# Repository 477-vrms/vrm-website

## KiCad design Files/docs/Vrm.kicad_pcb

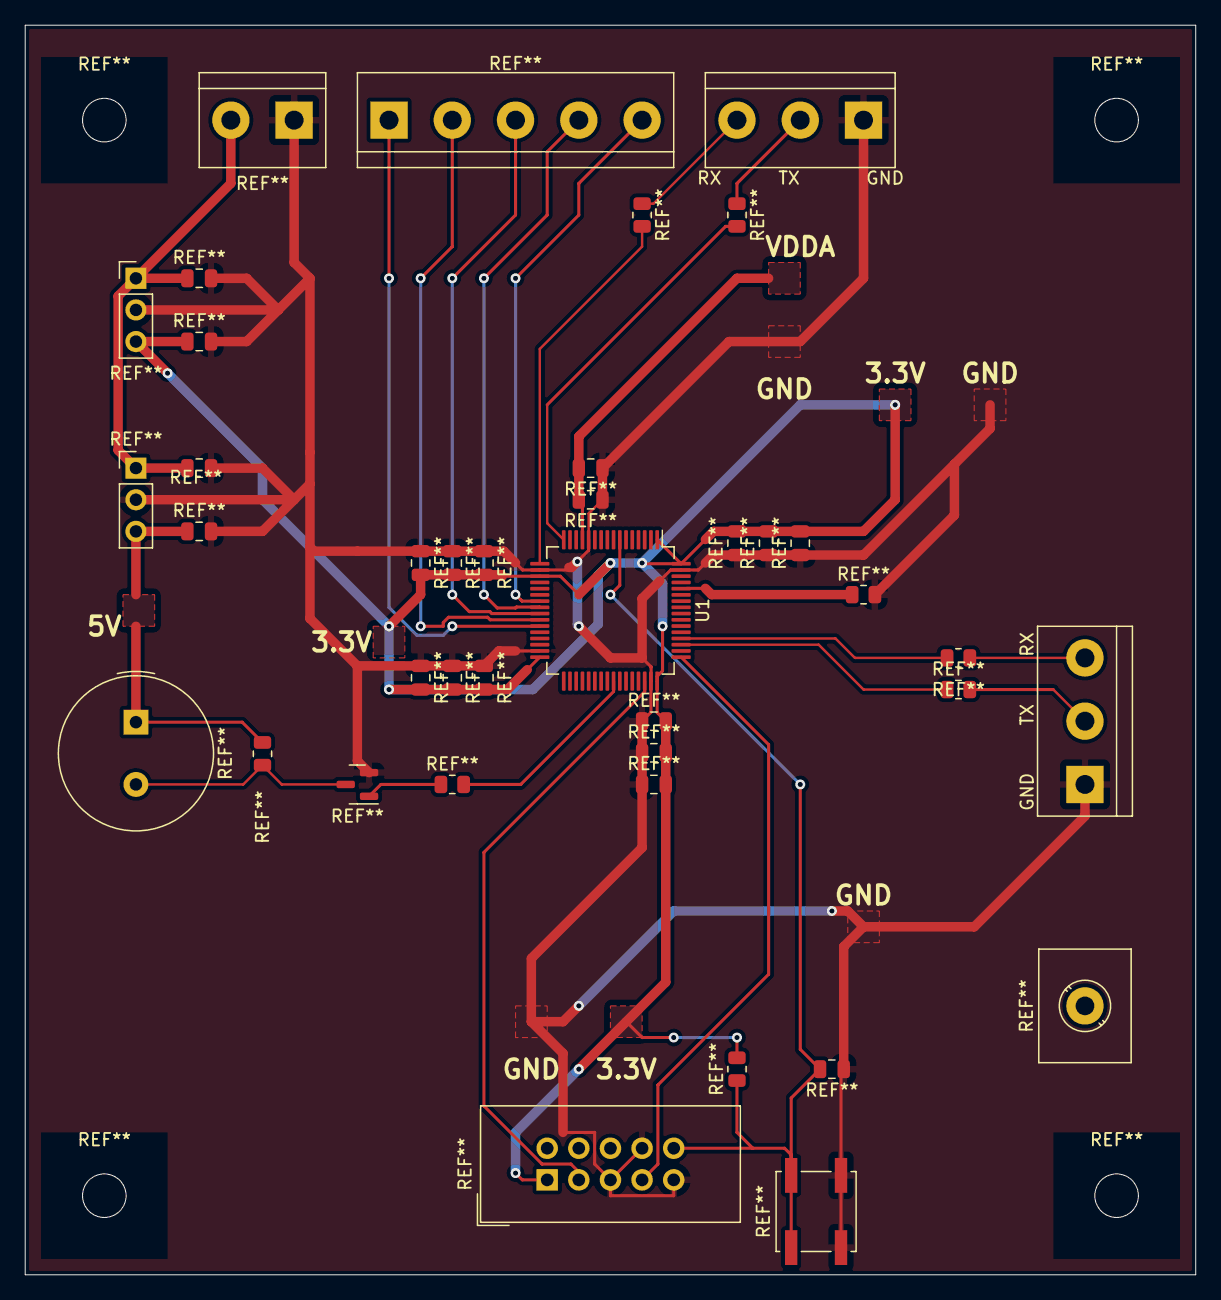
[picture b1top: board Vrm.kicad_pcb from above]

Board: 2 copper layers, 94.0 x 100.3 mm, 3 parts (0 on the bottom side), 2 nets.

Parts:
   RX      TX       GND: PI UART; TerminalBlock_bornier-3_P5.08mm
GND     TX     RX: Servo UART; TerminalBlock_bornier-3_P5.08mm
U1: STM32F091RCTx; LQFP-64_10x10mm_P0.5mm

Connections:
GND: RX TX GND.1, GND TX RX.1, U1.12 (VSSA), U1.18 (VSS), U1.31 (VSS), U1.47 (VSS), U1.63 (VSS)
VDD: U1.1 (VBAT), U1.19 (VDD), U1.32 (VDD), U1.48 (VDDIO2), U1.64 (VDD)

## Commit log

2022-01-19 Updated source link
2022-01-19 added github actions and edited the nav bar
2022-01-19 added github actions and edited the nav bar (#1)
2022-01-20 Added Changes for Matthew Wen
2022-01-20 Added Changes for Matthew Wen (#2)
2022-01-20 with document
2022-01-20 protyping potentially new website
2022-01-20 Brian profile
    member 2
2022-01-20 Update navbar.html
    oop
2022-01-21 Finished Writing Report
2022-01-21 Matt Wen Finished Writing Report (#3)
2022-01-21 Added James Information
2022-01-21 progress report
2022-01-21 prog report
2022-01-21 James' Week 2 Progress Report Created
2022-01-21 added documents
2022-01-26 Updated Content * Added PSSE onto website * Updated Header * Updated Final Proposal
2022-01-26 Updated Content (#4)
    * Added PSSE onto website
    * Updated Header
    * Updated Final Proposal
2022-01-27 added table of contents to my report
2022-01-27 added table of contents to my report (#5)
2022-01-27 progress report part 1
2022-01-28 Week3Progress
2022-01-28 Update3Progress
2022-01-28 Final Update
2022-01-28 week 3
2022-01-28 finished progress report
2022-01-28 Matthew Wen Week 3 Progress Report (#6)
2022-01-28 made links more visible on my website
2022-01-28 made links more visible on matt wen's website (#7)
2022-01-31 Update teams.html * Made Each Member Round * Updated the team.html file base to ../
2022-01-31 Update teams.html (#8)
    * Made Each Member Round
    * Updated the team.html file base to ../
2022-01-31 added doc
2022-02-04 week 4
2022-02-05 current progress report is up
2022-02-05 All ready to go
2022-02-05 Progress Report Week 4 (#9)
    * current progress report is up
    * All ready to go
2022-02-11 put wen101 instead of progress3
2022-02-11 Matt Wen Progress Report (#10)
    * current progress report is up
    * All ready to go
    * Finished Progress Report
    * put wen101 instead of progress3
2022-02-11 week5
2022-02-16 Added Pictures for Home Page
2022-02-16 New Images
2022-02-16 Added Pictures for Home Page (#11)
2022-02-17 finished week 6 report
2022-02-17 added final changes
2022-02-17 finished week 6 report (#13)
    * finished week 6 report
    * added final changes
2022-02-17 table of contents?
2022-02-17 Week 6
2022-02-19 Updagte progress4.html
2022-02-23 hello
2022-02-25 Done with Matt Wen Progress Report
2022-02-25 added final touches
2022-02-25 Matt Wen Progress Report (#14)
    * Done with Matt Wen Progress Report
    * added final touches
2022-02-27 Week 7 update
2022-02-27 Img update
2022-03-02 Added KiCad files to docs
2022-03-03 presentation
2022-03-11 Added updated PCB files to docs
2022-03-11 Updated docs
2022-03-11 I finished report
2022-03-11 I finished report (#15)
2022-03-25 Updated weekly progress
2022-03-25 idk im being forced to do this
2022-03-26 Matt Wen Progress Report (#16)
    * I finished report
    * finished progress report
2022-04-01 week12
2022-04-02 Finished Matt Wen Lab Report
2022-04-02 Finished Matt Wen Lab Report (#17)
2022-04-05 current progress as of tuesday
2022-04-07 week13
2022-04-08 Finished
2022-04-08 Matthewwen progress (#18)
    * current progress as of tuesday
    * Finished
2022-04-15 week
2022-04-15 new_progress
2022-04-16 Finished Matt Wen Progress Report
2022-04-16 Finished Matt Wen Progress Report (#19)
2022-04-22 Matthew Wen Progress Report Plus Trying to Add Video
2022-04-22 Matthew Wen Progress Report Plus Trying to Add Video (#20)
2022-04-26 Added Video Media
2022-04-26 Added Video Media (#21)
2022-04-26 Fixed Layout
2022-04-26 Fixed Layout (#22)
2022-04-26 added files
2022-04-30 final thinignhgds
2022-05-01 Week 16 Lab Report
2022-05-01 Week 16 Lab Report (#23)
2022-05-02 Getting Rid of Base from html
2022-05-03 Added Photos and Videos to the showcase screen
2022-05-04 Updated Sources
2022-05-05 Project Archived
2022-05-05 Updated Table of Contents for Brian and James
